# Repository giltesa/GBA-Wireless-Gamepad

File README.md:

# Game Boy Advance: Bluetooth HID Gamepad

### DESCRIPTION
This simple circuit allows you to connect an **ESP32** to the Link Cable port of the **Game Boy Advance** or **Game Boy Advance SP**, giving it **bluetooth** connectivity and turning it into a Human Interface Device (**HID**) so it can be used as a **bluetooth gamepad** and connected to a computer or phone to control games from the GBA.

### REQUIRED
*   1x Game Boy Advance Wireless Adapter (shell & connector)
*   1x PCB (Download the Gerber files and order it yourself, PCB Thickness: 1mm)
*   1x ESP-WROOM-32 ESP32-WROOM-NARROW
*   1x Resistor 0603 1K
*   2x Resistor 0603 10K
*   1x LED 0603
*   2x Switch bottom 4.6\*2.8mm
*   1x USB UART-CP2102 **(1)**

**(1)** This [USB UART adapter](https://www.aliexpress.com/item/1005009534233685.html) can be connected directly to the board without the need for cables or soldering. Just connect it and keep both boards at a 45-degree angle so all the pins make electrical contact. Hold them together with a rubber band and, after programming the code, disconnect the boards.

### NOTES
I had a lot of difficulties in 2020 trying to flash the code onto the ESP32, and I eventually gave up without succeeding. Now, in 2026, I gave it another try and finally managed to do it, but it is still quite complicated for anyone not familiar with ESP32 development tools.

**Shyri Villar**’s code needs to be compiled to generate the .bin file, and once you have it, it must be flashed onto the ESP32. To simplify the process, I uploaded the already compiled .bin file to my repository, so the only remaining step is flashing it onto the ESP32. I also uploaded instructions to help with that task.

### ATTRIBUTIONS
The original idea is not mine, but [**Shyri Villar**](https://github.com/Shyri)’s, who designed it for a GBA to NGC cable and developed the software. I only adapted it to work with the GBA wireless adapter.

### LICENSE
This project is licensed under a **Creative Commons** license:
**[Attribution-NonCommercial-ShareAlike 4.0 International (CC BY-NC-SA 4.0) ](https://creativecommons.org/licenses/by-nc-sa/4.0/)**

Check the [LICENSE.md](LICENSE.md) for more information.

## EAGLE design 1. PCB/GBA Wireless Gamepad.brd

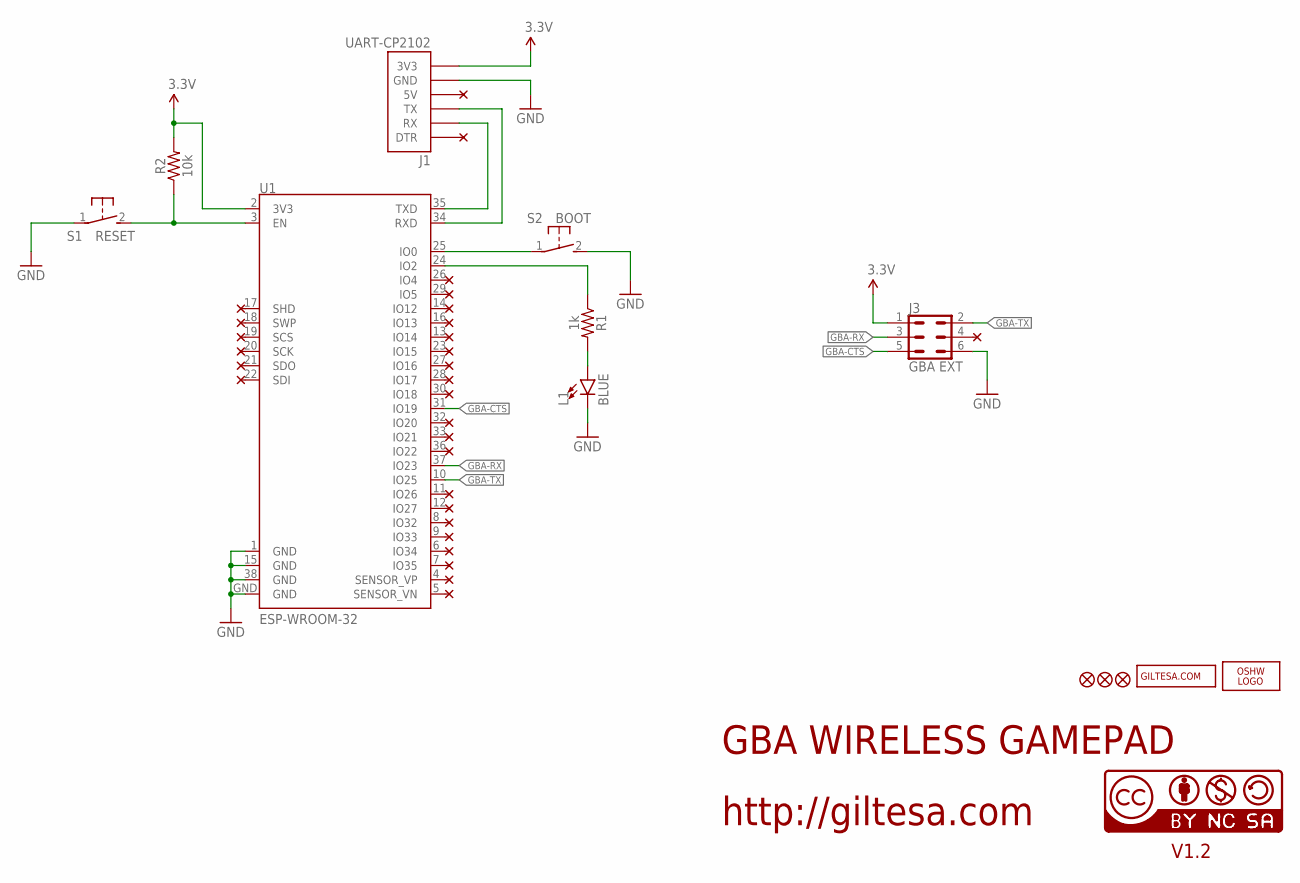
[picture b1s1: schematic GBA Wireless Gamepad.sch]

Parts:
J1: UART-CP2102
J3: GBA EXT; GBA_EXT
L1: BLUE; LED-0603
LOGO1: OSHW_LOGO_FILLX0150-NT; OSHW_FILLX150_NOTEXT
R1: 1k; R0603
R2: 10k; R0603
S1: RESET; SWITCH_SMD_4.6X2.8MM
S2: BOOT; SWITCH_SMD_4.6X2.8MM
U1: ESP-WROOM-32; ESP32-WROOM-NARROW
U$6, U$7, U$14: FIDUCIAL1X2; FIDUCIAL-1X2
U$10: GILTESA.COM_MASK; GILTESA.COM_MASK_15MM
U$17: CC-NC-BCNIX; CC-NC-B_NIX

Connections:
3.3V: J1.3V3, J3.1, R2.2, U1.2 (3V3)
CHIP_PU: R2.1, S1.2 (B), U1.3 (EN)
GBA-CTS: J3.5, U1.31 (IO19)
GBA-RX: J3.3, U1.37 (IO23)
GBA-TX: J3.2, U1.10 (IO25)
GND: J1.GND, J3.6, L1.C, S1.1 (A), S2.2 (B), U1.1 (GND), U1.15 (GND), U1.38 (GND), U1.GND
unnamed: S2.1 (A), U1.25 (IO0)
unnamed: L1.A, R1.2
unnamed: R1.1, U1.24 (IO2)
RX: J1.TX, U1.34 (RXD)
TX: J1.RX, U1.35 (TXD)

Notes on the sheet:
GBA WIRELESS GAMEPAD
http://giltesa.com
V1.2

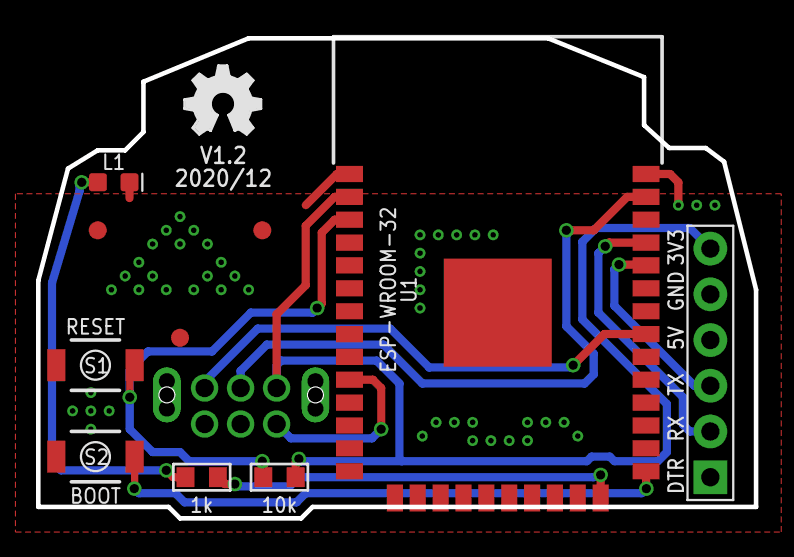
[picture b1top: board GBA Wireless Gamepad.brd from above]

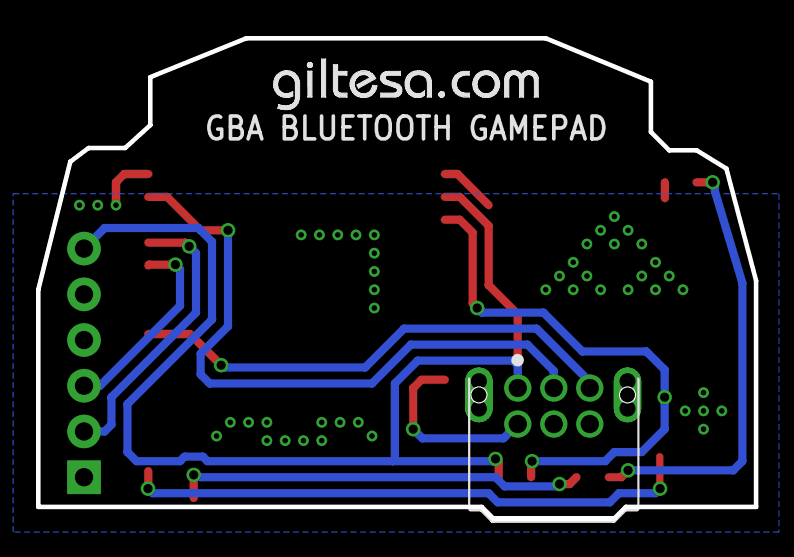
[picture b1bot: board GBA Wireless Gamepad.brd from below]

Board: 2 copper layers, 39.9 x 26.7 mm, 14 parts (2 on the bottom side), 11 nets.

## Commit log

2021-02-21 v1.0
2021-02-21 v1.2
2021-02-21 no message
2026-05-01 Moved the original code to another folder.
2026-05-01 ESP32 image with LED status indicator

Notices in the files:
parts and their libraries:
SparkFun: Licensing: CC v3.0 Share-Alike You are welcome to use this library for commercial purposes.
SparkFun-LED: Licensing: Creative Commons ShareAlike 4.0 International - https://creativecommons.org/licenses/by-sa/4.0
cc-by-nc-sa: All hardware is licensed under the Creative Commons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
